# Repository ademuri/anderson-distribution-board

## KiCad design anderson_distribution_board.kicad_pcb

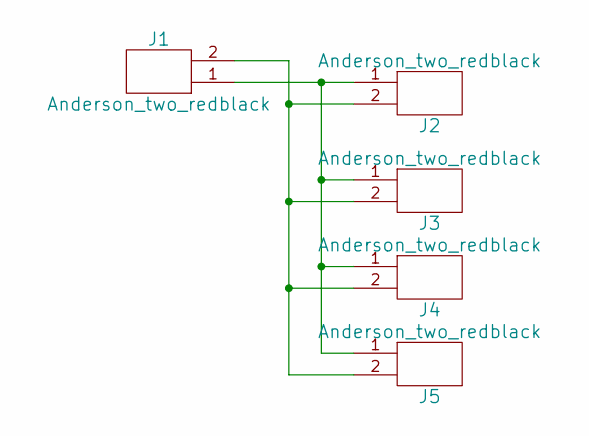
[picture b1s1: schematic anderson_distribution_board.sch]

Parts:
J1: Anderson_two_redblack; Anderson_1337G3_right_angle_bottom_two
J2, J3, J4, J5: Anderson_two_redblack; Anderson_1337G3_straight_two

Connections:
unnamed: J1.1, J2.1, J3.1, J4.1, J5.1
unnamed: J1.2, J2.2, J3.2, J4.2, J5.2

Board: 2 copper layers, 5 parts (0 on the bottom side), 2 nets, no tracks yet.

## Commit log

2018-06-15 Polish and add gerbers
